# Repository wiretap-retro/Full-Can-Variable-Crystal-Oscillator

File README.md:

# Full Can Variable Crystal Oscillator
A full can size crystal oscillator that can be programmed for the frequency you need.

\

## Info
This variable crystal oscillator in a full-can form factor can be programmed from frequencies 8kHz to 160MHz. An arduino or pi can easily be used to hook up to the i2c port to set the frequency. Use a 3.3V SMD crystal oscillator and install into a 5V system.
\
\
This project is based on the Adafruit Si5351 found here: https://learn.adafruit.com/adafruit-si5351-clock-generator-breakout
\
Vogons thread for more info: https://www.vogons.org/viewtopic.php?t=82731

## Programming
The Adafruit tutorial found here is how this device is programmed: https://learn.adafruit.com/adafruit-si5351-clock-generator-breakout/wiring-and-test \
In-circuit programmer hat: https://github.com/wiretap-retro/Full-Can-Variable-Programmer/

## Notes
This project does not utilize the clock enable pin (EN on most datasheets), so it can only be used in parent boards that don't make active use of the clock enable/disable function.

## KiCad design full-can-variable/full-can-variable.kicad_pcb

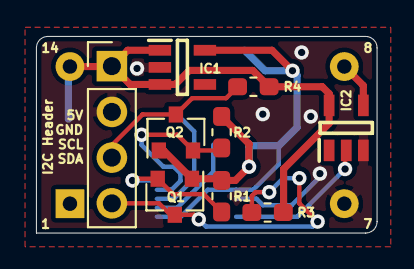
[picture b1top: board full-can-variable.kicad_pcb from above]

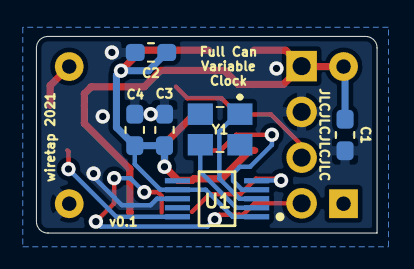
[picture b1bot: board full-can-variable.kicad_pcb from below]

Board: 2 copper layers, 18.9 x 10.9 mm, 16 parts (6 on the bottom side), 11 nets.

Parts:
C1: 1uF; C_0603_1608Metric_Pad1.05x0.95mm_HandSolder
C2: 0.1uF; C_0603_1608Metric_Pad1.05x0.95mm_HandSolder
C3, C4: 0.47uF; C_0603_1608Metric_Pad1.05x0.95mm_HandSolder
I2C Header: I2C; PinHeader_1x04_P2.54mm_Vertical
IC1: IC1; SOT95P275X110-5N
IC2: IC2; SOT95P280X145-5N
Q1, Q2: BSS138-G; SOT-23
R1, R2, R3, R4: 10k; R_0603_1608Metric_Pad1.05x0.95mm_HandSolder
U1: U1; Silicon_Laboratories-SI5351A-B02075-GT-0
X1: CXO_DIP14; Oscillator_DIP-14
Y1: Y1; ABM8G48000MHZ18D2YT

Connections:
/3VCLK: IC2.2, U1.10
/5VCLK: IC2.4, X1.8
/SCL_3V: Q2.2, R2.2, U1.4
/SCL_5V: I2C Header.3, Q2.3, R4.2
/SDA_3V: Q1.2, R1.2, U1.5
/SDA_5V: I2C Header.4, Q1.3, R3.2
/VDD: C2.1, C3.2, C4.2, IC1.5, Q1.1, Q2.1, R1.1, R2.1, U1.1, U1.7
/VIN: C1.1, I2C Header.1, IC1.1, IC1.3, IC2.5, R3.1, R4.1, X1.14
GND: C1.2, C2.2, C3.1, C4.1, I2C Header.2, IC1.2, IC2.3, U1.8, X1.7
unnamed: U1.2, Y1.3
unnamed: U1.3, Y1.1

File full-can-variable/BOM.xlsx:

Reference | Value | Footprint | Description | Manufacturer | Mouser Part Number
C1, C2 | 1uF | Capacitor_SMD:C_0603_1608Metric_Pad1.05x0.95mm_HandSolder | 0603 1uF Capacitor SMD | Taiyo Yuden | 963-LMK107B7105KAHT
C3, C4 | 0.47uF | Capacitor_SMD:C_0603_1608Metric_Pad1.05x0.95mm_HandSolder | 0603 0.47uF Capacitor SMD | Samsung | 187-CL10B474KO8VPNC
IC1 | NCP164CSN330T1G | SOT95P275X110-5N | LDO Regulator Pos 3.3V 0.3A 5-Pin TSOP T/R | ON Semiconductor | 863-NCP164CSN330T1G
IC2 | SN74LV1T34DBVRG4 | SOT95P280X145-5N | Single Power Supply BUFFER Logic Level Shifter (no enable) | Texas Instruments | 595-SN74LV1T34DBVRG4
J1 | I2C | Connector_PinHeader_2.54mm:PinHeader_1x04_P2.54mm_Vertical | 1x04 2.54mm Pin Header | TE Connectivity | 571-5-103327-1
Q1, Q2 | BSS138-G | Package_TO_SOT_SMD:SOT-23 | BSS138 MOSFET | Onsemi | 863-BSS138-G
R1 - R4 | 10k | Resistor_SMD:R_0603_1608Metric_Pad1.05x0.95mm_HandSolder | 0603 10k ohm Resistor SMD | Vishay | 71-CRCW060310K0JNEAC
U1 | SI5351A-B02075-GT | SamacSys_Parts:Silicon_Laboratories-SI5351A-B02075-GT-0 | Programmable Clock Generator (MSOP-10 package) | Skyworks Solutions | 634-SI5351A-B02075GT
Y1 | ABM8G-25.000MHZ-4Y-T3 | ABM8G48000MHZ18D2YT | Abracon 25MHz Crystal Unit +/-30ppm SMD 4-Pin 3.2 x 2.5 x 1mm | ABRACON | 815-ABM8G-25-4YT3
